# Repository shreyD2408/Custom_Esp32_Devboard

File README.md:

# SD2408 Devboard V1

When designing compact mobile robots, such as miniature rovers, self-balancing walkers, or desktop mecanum platforms—builders almost universally hit a frustrating physical bottleneck: the "breadboard jungle." Connecting an ESP32 microcontroller to external motor drivers, motion sensors, audio amplifiers, and servo breakout boards usually requires a rats' nest of jumper wires, perfboards, and loose cables. Every vibration from a motor risks shaking a loose DuPont connector loose, leading to intermittent power faults, debugging nightmares, and fragile hardware.

This project was built to solve that exact pain point from the ground up: an all-in-one, purpose-built development board that integrates every essential subsystem needed for intelligent, agile robotics onto a single, robust printed circuit board.

# How it Works

1. ESP32-S3-MINI-1: Processes information, reads data, and sends data to different parts of the board through firmware.
2. Motor Drivers: Control power and polarity of the brushed DC motors using either the USB-C power or external 5V input.
3. Four motor terminal connectors: Provide connection points for the DC motors for intended motor configuration.
4. Power Output Points: Designated 5V and GND power outputs for external components.
5. MPU6050: Measures tilt in radians (or if converted, degrees), and acceleration.
6. Audio output: Allows a compatible speaker to produce sound through the board's audio circuitry.

The components are connected through a custom-designed schematic and PCB layout. The schematic defines the electrical connections, while the PCB layout determines where components sit and how electrical signals travel through copper traces.

# Schematic

The schematic shows the electrical connection between all built-in components. Editable schematic available in the **hardware** folder.

# PCB Layout

# 3D Model

The 3D Model shows the physical placement of components, copper traces, and connectors. Editable 3D Model available in the **hardware** folder.

# How to use

Connect the board to a computer through USB-C to program the ESP32-S3 using the Arduino IDE or ESP-IDF. Upload firmware onto the board provided in "firmware" folder for basic features. Firmware can then be used to control motors and servos, read motion data from the MPU6050, and play audio through the MAX98357A amplifier.

External components can be connected through the dedicated motor terminals, servo headers, power outputs, and GPIO, ADC, and I2C headers. Alternatively, a suitable external 5V supply can be connected through the power terminal block. Verify the board's power requirements before connecting motors or servos.

## Bill of Materials (BOM)

| Part | Purpose | Qty | Unit Cost | Total | Vendor |
|---|---|---:|---:|---:|---|
| Panasonic Push Button | User input, BOOT/RESET | 5 | $0.38 | $1.90 | LCSC |
| Ceramic 1µF Capacitor | Decoupling | 50 | $0.01 | $0.50 | LCSC |
| Ceramic 2.2µF Capacitor | Decoupling | 20 | $0.02 | $0.40 | LCSC |
| Ceramic 10µF Capacitor | Filtering | 20 | $0.03 | $0.60 | LCSC |
| Ceramic 100nF Capacitor | Decoupling | 50 | $0.01 | $0.50 | LCSC |
| Ceramic 10nF Capacitor | Filtering | 50 | $0.01 | $0.50 | LCSC |
| Ceramic 220nF Capacitor | Filtering | 2 | $0.33 | $0.66 | LCSC |
| USB-C Connector | Power and programming | 20 | $0.08 | $1.60 | LCSC |
| ESD Protection Diode | Surge protection | 20 | $0.03 | $0.60 | LCSC |
| Fuse | Overcurrent protection | 5 | $0.09 | $0.45 | LCSC |
| MAX98357A | Audio amplifier | 1 | $1.33 | $1.33 | LCSC |
| DRV8833PW | Motor driver | 2 | $1.65 | $3.30 | LCSC |
| LM1117 | 5V to 3.3V regulator | 5 | $0.18 | $0.90 | LCSC |
| USBLC6-2SC6 | USB ESD protection | 10 | $0.05 | $0.50 | LCSC |
| 10K Resistor | Passive component | 100 | $0.01 | $1.00 | LCSC |
| 2.2K Resistor | Passive component | 100 | $0.01 | $1.00 | LCSC |
| 5.1K Resistor | Passive component | 100 | $0.01 | $1.00 | LCSC |
| 1M Resistor | Passive component | 100 | $0.01 | $1.00 | LCSC |
| 1K Resistor | Passive component | 100 | $0.01 | $1.00 | LCSC |
| ESP32-S3-MINI-1 | Main MCU and Wi-Fi | 1 | $4.76 | $4.76 | LCSC |
| 1×2 Terminal Block | Power and motor input | 5 | $0.10 | $0.50 | LCSC |
| 1×3 Terminal Block | Power output | 5 | $0.35 | $1.75 | LCSC |
| LED | Power indicator | 100 | $0.01 | $1.00 | LCSC |
| Custom PCB | Component mounting | 5 | $2.60 | $13.00 | JLCPCB |

**Links available in BOM.md**

### Cost Summary

| Item | Cost |
|---|---:|
| Parts Subtotal | $39.75 |
| Tax & Shipping | $17.36 |
| **Grand Total** | **$57.11 USD** |

**Disclaimer** - Quantities are not exact as LCSC sells in bulk.

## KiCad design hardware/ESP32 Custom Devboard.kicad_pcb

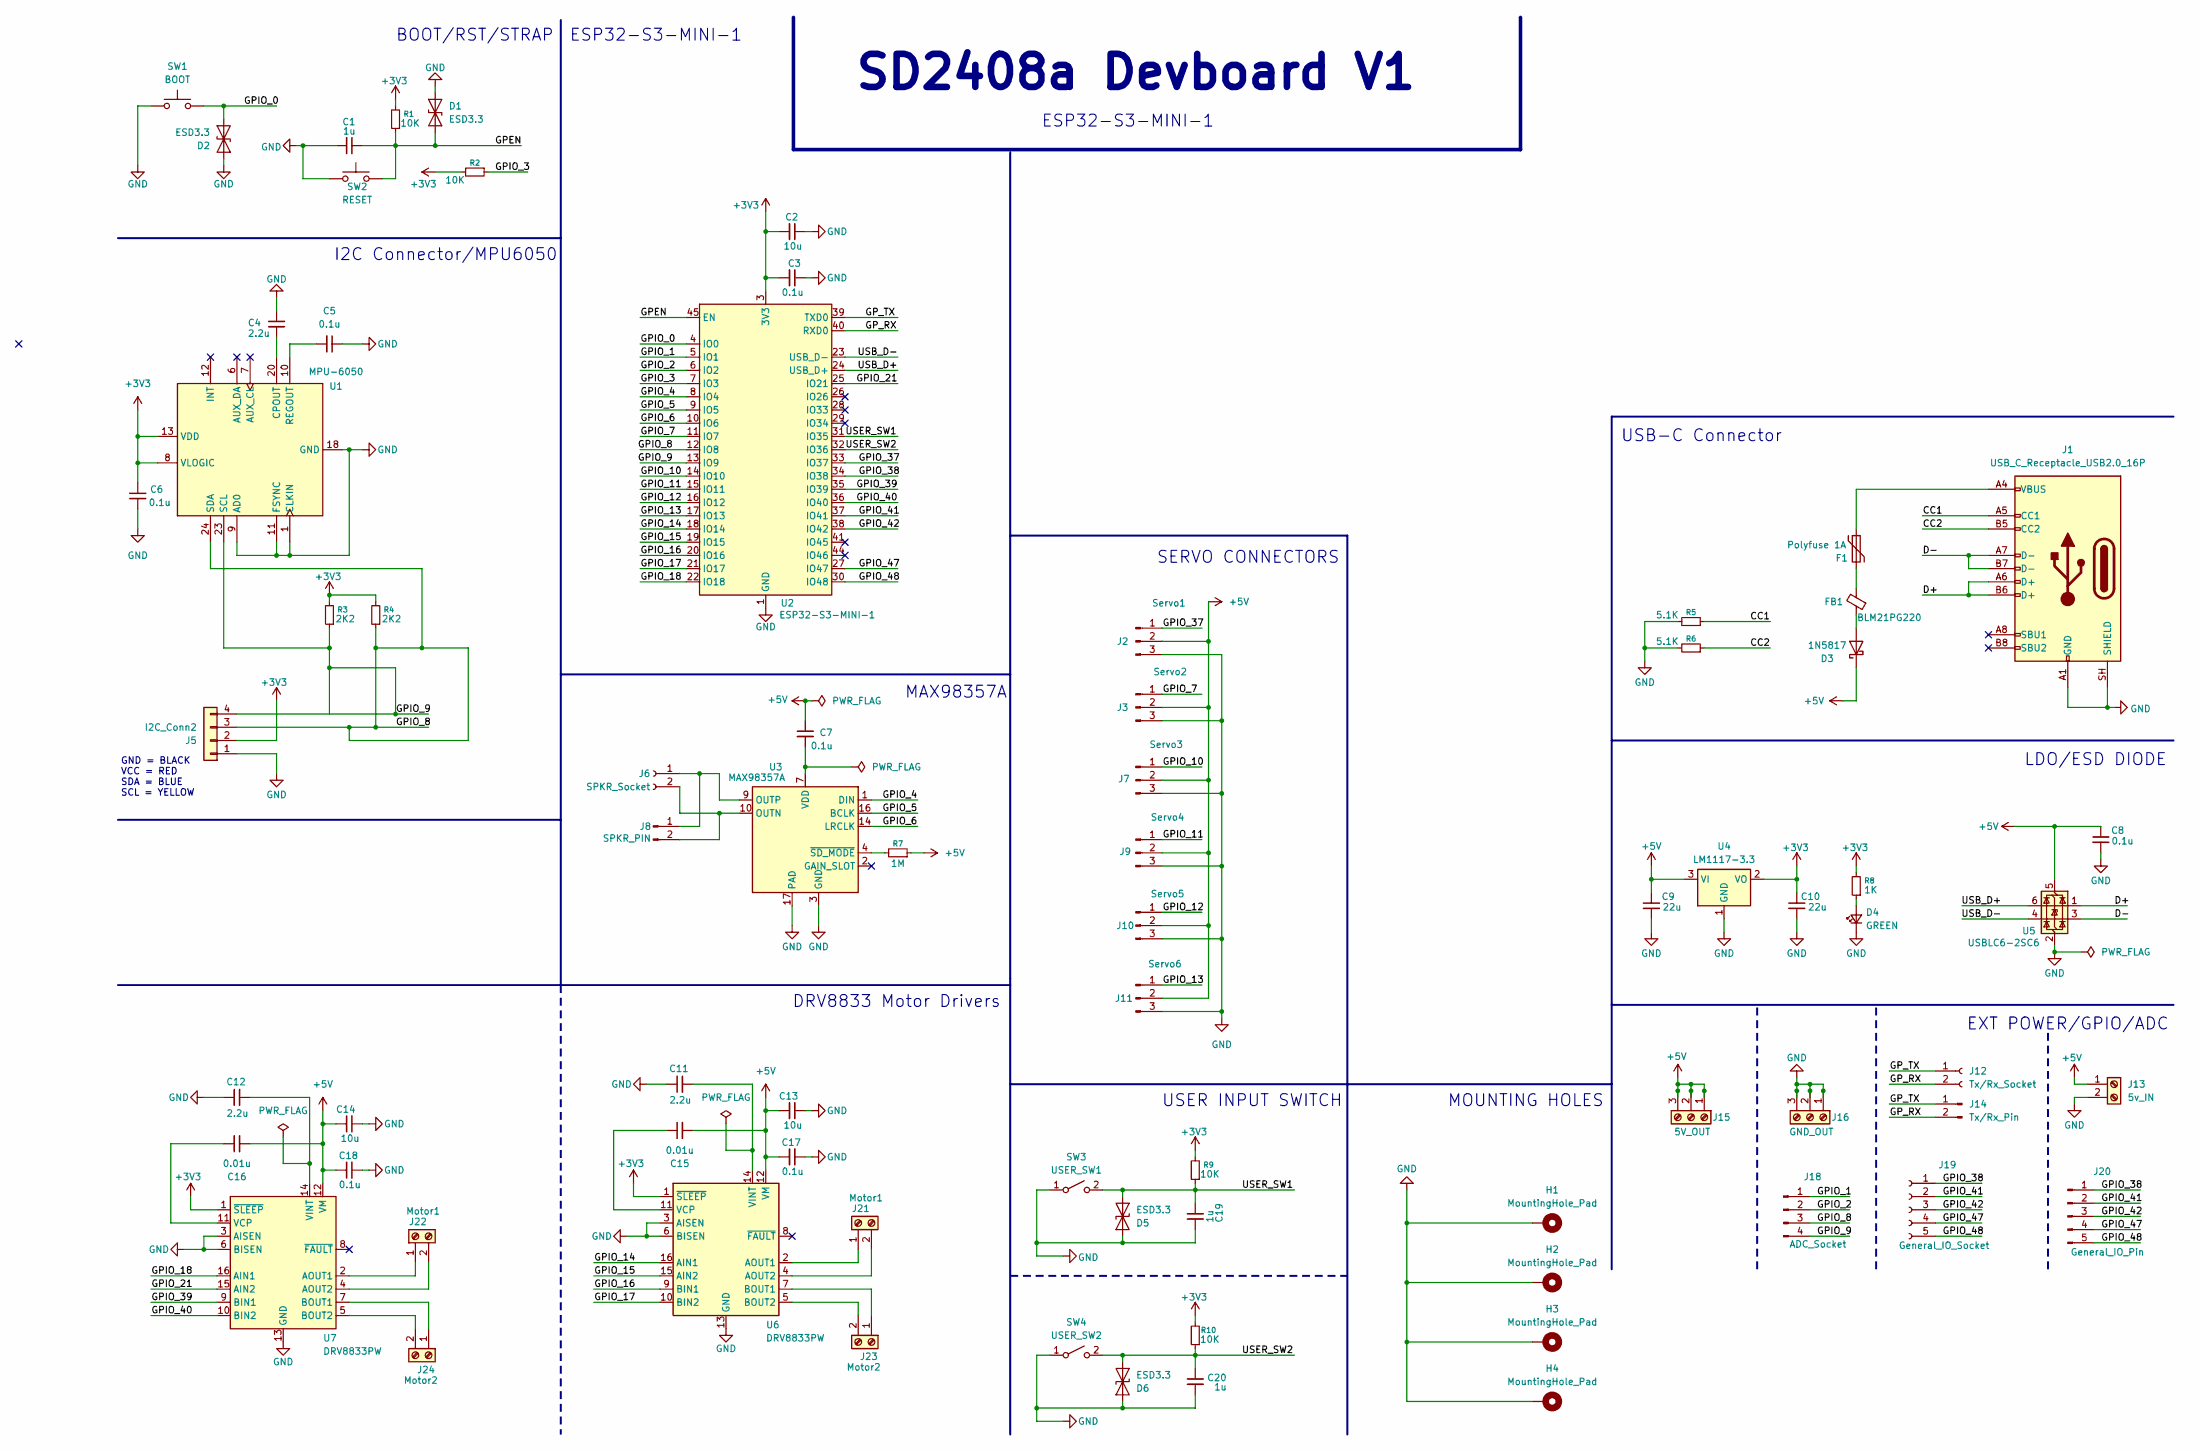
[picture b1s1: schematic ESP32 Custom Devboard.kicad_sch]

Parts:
C1, C19, C20: 1u; C_0201_0603Metric_Pad0.64x0.40mm_HandSolder
C2, C13, C14: 10u; C_0402_1005Metric_Pad0.74x0.62mm_HandSolder
C3, C5, C6, C7, C8, C17, C18: 0.1u; C_0402_1005Metric_Pad0.74x0.62mm_HandSolder
C4, C11, C12: 2.2u; C_0201_0603Metric_Pad0.64x0.40mm_HandSolder
C9, C10: 22u; C_1825_4564Metric_Pad1.57x6.80mm_HandSolder
C15, C16: 0.01u; C_1206_3216Metric_Pad1.33x1.80mm_HandSolder
D1, D2, D5, D6: ESD3.3; D_SOD-923
D3: 1N5817; D_DO-41_SOD81_P10.16mm_Horizontal
D4: GREEN; LED_0402_1005Metric_Pad0.77x0.64mm_HandSolder
F1: Polyfuse 1A; Fuse_1206_3216Metric
FB1: BLM21PG220; L_0805_2012Metric_Pad1.05x1.20mm_HandSolder
H1, H2, H3, H4: MountingHole_Pad; MountingHole_3.2mm_M3_DIN965_Pad
J1: USB_C_Receptacle_USB2.0_16P; USB_C_Receptacle_HCTL_HC-TYPE-C-16P-01A
J2: Servo1; PinHeader_1x03_P2.54mm_Vertical
J3: Servo2; PinHeader_1x03_P2.54mm_Vertical
J5: I2C_Conn2; PinSocket_1x04_P2.54mm_Vertical
J6: SPKR_Socket; PinSocket_1x02_P2.54mm_Vertical
J7: Servo3; PinHeader_1x03_P2.54mm_Vertical
J8: SPKR_PIN; PinHeader_1x02_P2.54mm_Vertical
J9: Servo4; PinHeader_1x03_P2.54mm_Vertical
J10: Servo5; PinHeader_1x03_P2.54mm_Vertical
J11: Servo6; PinHeader_1x03_P2.54mm_Vertical
J12: Tx/Rx_Socket; PinSocket_1x02_P2.54mm_Vertical
J13: 5v_IN; TerminalBlock_4Ucon_1x02_P3.50mm_Horizontal
J14: Tx/Rx_Pin; PinHeader_1x02_P2.54mm_Vertical
J15: 5V_OUT; TerminalBlock_Xinya_XY308-2.54-3P_1x03_P2.54mm_Horizontal
J16: GND_OUT; TerminalBlock_Xinya_XY308-2.54-3P_1x03_P2.54mm_Horizontal
J18: ADC_Socket; PinSocket_1x04_P2.54mm_Vertical
J19: General_IO_Socket; PinSocket_1x05_P2.54mm_Vertical
J20: General_IO_Pin; PinHeader_1x05_P2.54mm_Vertical
J21, J22: Motor1; TerminalBlock_4Ucon_1x02_P3.50mm_Horizontal
J23, J24: Motor2; TerminalBlock_4Ucon_1x02_P3.50mm_Horizontal
R1, R2, R9, R10: 10K; R_0402_1005Metric_Pad0.72x0.64mm_HandSolder
R3, R4: 2K2; R_0402_1005Metric_Pad0.72x0.64mm_HandSolder
R5, R6: 5.1K; R_0402_1005Metric_Pad0.72x0.64mm_HandSolder
R7: 1M; R_0402_1005Metric_Pad0.72x0.64mm_HandSolder
R8: 1K; R_0402_1005Metric_Pad0.72x0.64mm_HandSolder
SW1: BOOT; DIP-24_W7.62mm
SW2: RESET; DIP-24_W7.62mm
SW3: USER_SW1; SW_SPST_EVQP2_ShortPushTravel_H2.1mm
SW4: USER_SW2; SW_SPST_EVQP2_ShortPushTravel_H2.1mm
U1: MPU-6050; InvenSense_QFN-24_4x4mm_P0.5mm
U2: ESP32-S3-MINI-1; ESP32-S2-MINI-1
U3: MAX98357A; TQFN-16-1EP_3x3mm_P0.5mm_EP1.23x1.23mm
U4: LM1117-3.3; SOT-223-3_TabPin2
U5: USBLC6-2SC6; SOT-23-6
U6, U7: DRV8833PW; TSSOP-16_4.4x5mm_P0.65mm

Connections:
+3V3: C2.2, C3.2, C6.1, C10.1, J5.2, R1.2, R2.2, R3.2, R4.2, R8.2, R9.2, R10.2, U1.8 (VLOGIC), U1.13 (VDD), U2.3 (3V3), U4.2 (VO), U6.1 (~SLEEP), U7.1 (~SLEEP)
+5V: C7.2, C8.1, C9.1, C13.2, C14.2, C15.2, C16.2, C17.2, C18.2, D3.1 (K), J2.2, J3.2, J7.2, J9.2, J10.2, J11.2, J13.1, J15.1, J15.2, J15.3, R7.1, U4.3 (VI), U5.5 (VBUS), U6.12 (VM), U7.12 (VM)
/CC1: J1.A5 (CC1), R5.1
/CC2: J1.B5 (CC2), R6.1
/D+: J1.A6 (D+), J1.B6 (D+), U5.1 (I/O1)
/D-: J1.A7 (D-), J1.B7 (D-), U5.3 (I/O2)
/GPEN: C1.1, D1.1 (A1), R1.1, SW2.2 (B), U2.45 (EN)
/GPIO_0: D2.1 (A1), SW1.2 (B), U2.4 (IO0)
/GPIO_1: J18.1, U2.5 (IO1)
/GPIO_2: J18.2, U2.6 (IO2)
/GPIO_3: R2.1, U2.7 (IO3)
/GPIO_4: U2.8 (IO4), U3.1 (DIN)
/GPIO_5: U2.9 (IO5), U3.16 (BCLK)
/GPIO_6: U2.10 (IO6), U3.14 (LRCLK)
/GPIO_7: J3.1, U2.11 (IO7)
/GPIO_8: J5.3, J18.3, R4.1, U1.24 (SDA), U2.12 (IO8)
/GPIO_9: J5.4, J18.4, R3.1, U1.23 (SCL), U2.13 (IO9)
/GPIO_10: J7.1, U2.14 (IO10)
/GPIO_11: J9.1, U2.15 (IO11)
/GPIO_12: J10.1, U2.16 (IO12)
/GPIO_13: J11.1, U2.17 (IO13)
/GPIO_14: U2.18 (IO14), U6.16 (AIN1)
/GPIO_15: U2.19 (IO15), U6.15 (AIN2)
/GPIO_16: U2.20 (IO16), U6.9 (BIN1)
/GPIO_17: U2.21 (IO17), U6.10 (BIN2)
/GPIO_18: U2.22 (IO18), U7.16 (AIN1)
/GPIO_21: U2.25 (IO21), U7.15 (AIN2)
/GPIO_37: J2.1, U2.33 (IO37)
/GPIO_38: J19.1, J20.1, U2.34 (IO38)
/GPIO_39: U2.35 (IO39), U7.9 (BIN1)
/GPIO_40: U2.36 (IO40), U7.10 (BIN2)
/GPIO_41: J19.2, J20.2, U2.37 (IO41)
/GPIO_42: J19.3, J20.3, U2.38 (IO42)
/GPIO_47: J19.4, J20.4, U2.27 (IO47)
/GPIO_48: J19.5, J20.5, U2.30 (IO48)
/GP_RX: J12.2, J14.2, U2.40 (RXD0)
/GP_TX: J12.1, J14.1, U2.39 (TXD0)
/USB_D+: U2.24 (USB_D+), U5.6 (I/O1)
/USB_D-: U2.23 (USB_D-), U5.4 (I/O2)
/USER_SW1: C19.2, D5.1 (A1), R9.1, SW3.2 (B), U2.31 (IO35)
/USER_SW2: C20.2, D6.1 (A1), R10.1, SW4.2 (B), U2.32 (IO36)
GND: C1.2, C2.1, C3.1, C4.1, C5.2, C6.2, C8.2, C9.2, C10.2, C11.2, C12.2, C13.1, C14.1, C17.1, C18.1, C19.1, C20.1, D1.2 (A2), D2.2 (A2), D4.1 (K), D5.2 (A2), D6.2 (A2), H1.1 (1_1), H2.1 (1_1), H3.1 (1_1), H4.1 (1_1), J1.A1 (GND), J1.A12 (GND), J1.B1 (GND), J1.B12 (GND), J1.SH (SHIELD), J2.3, J3.3, J5.1, J7.3, J9.3, J10.3, J11.3, J13.2, J16.1, J16.2, J16.3, R5.2, R6.2, SW1.1 (A), SW2.1 (A), SW3.1 (A), SW4.1 (A), U1.1 (CLKIN), U1.9 (AD0), U1.11 (FSYNC), U1.18 (GND), U2.1 (GND), U2.2 (GND), U2.42 (GND), U2.43 (GND), U2.46 (GND), U2.47 (GND), U2.48 (GND), U2.49 (GND), U2.50 (GND), U2.51 (GND), U2.52 (GND), U2.53 (GND), U2.54 (GND), U2.55 (GND), U2.56 (GND), U2.57 (GND), U2.58 (GND), U2.59 (GND), U2.60 (GND), U2.61 (GND), U2.62 (GND), U2.63 (GND), U2.64 (GND), U2.65 (GND), U3.3 (GND), U3.11 (GND), U3.15 (GND), U3.17 (PAD), U4.1 (GND), U5.2 (GND), U6.3 (AISEN), U6.6 (BISEN), U6.13 (GND), U7.3 (AISEN), U7.6 (BISEN), U7.13 (GND)
unnamed: C7.1, U3.7 (VDD), U3.8 (VDD)
unnamed: D3.2 (A), FB1.1
unnamed: D4.2 (A), R8.1
unnamed: F1.1, J1.A4 (VBUS), J1.A9 (VBUS), J1.B4 (VBUS), J1.B9 (VBUS)
unnamed: F1.2, FB1.2
unnamed: J6.1, J8.1, U3.9 (OUTP)
unnamed: J6.2, J8.2, U3.10 (OUTN)
unnamed: J21.1, U6.2 (AOUT1)
unnamed: J21.2, U6.4 (AOUT2)
unnamed: J22.1, U7.2 (AOUT1)
unnamed: J22.2, U7.4 (AOUT2)
unnamed: J23.1, U6.7 (BOUT1)
unnamed: J23.2, U6.5 (BOUT2)
unnamed: J24.1, U7.7 (BOUT1)
unnamed: J24.2, U7.5 (BOUT2)
unnamed: C4.2, U1.20 (CPOUT)
unnamed: C5.1, U1.10 (REGOUT)
unnamed: R7.2, U3.4 (~SD_MODE)
unnamed: C15.1, U6.11 (VCP)
unnamed: C11.1, U6.14 (VINT)
unnamed: C16.1, U7.11 (VCP)
unnamed: C12.1, U7.14 (VINT)

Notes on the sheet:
DRV8833 Motor Drivers
MOUNTING HOLES
ESP32-S3-MINI-1
I2C Connector/MPU6050
SD2408a Devboard V1
ESP32-S3-MINI-1
MAX98357A
LDO/ESD DIODE
GND = BLACK VCC = RED SDA = BLUE SCL = YELLOW
EXT POWER/GPIO/ADC
BOOT/RST/STRAP
USER INPUT SWITCH
USB-C Connector
SERVO CONNECTORS

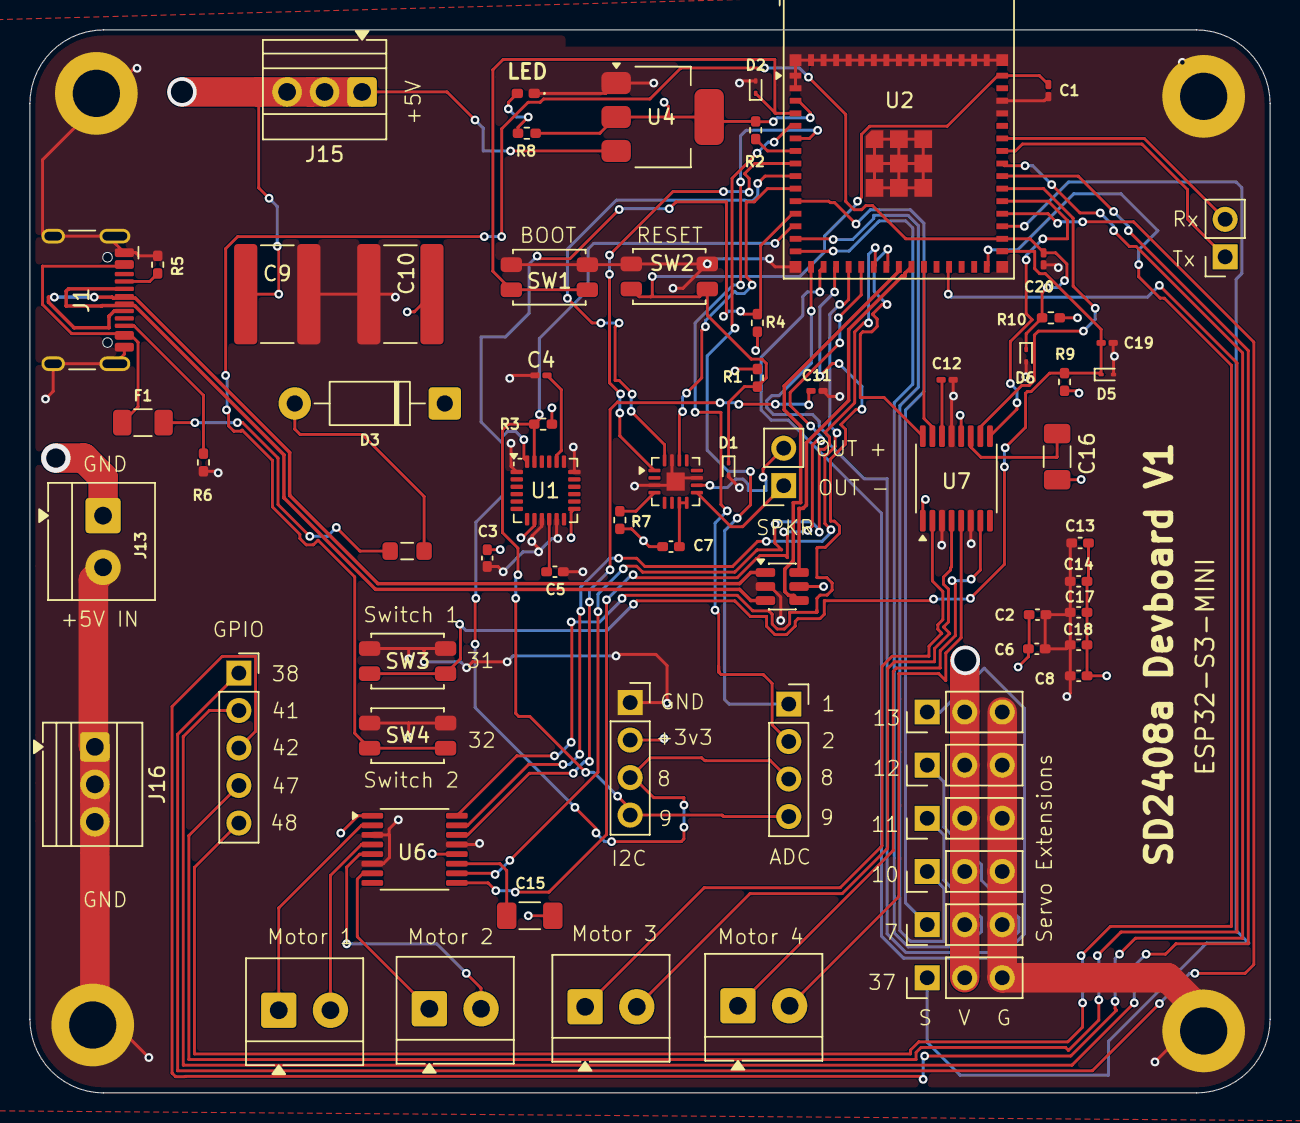
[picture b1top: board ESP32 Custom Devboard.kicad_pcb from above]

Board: 4 copper layers, 84.0 x 72.0 mm, 72 parts (0 on the bottom side), 64 nets.

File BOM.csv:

"Reference","Qty","Value","DNP","Exclude from BOM","Exclude from Board","Exclude from Simulation","Exclude from Position Files","Footprint","Datasheet"
"SW3","1","USER_SW1","","","","","${EXCLUDE_FROM_POS_FILES}","Button_Switch_SMD:SW_SPST_EVQP2_ShortPushTravel_H2.1mm",""
"SW4","1","USER_SW2","","","","","${EXCLUDE_FROM_POS_FILES}","Button_Switch_SMD:SW_SPST_EVQP2_ShortPushTravel_H2.1mm",""
"C1,C19,C20","3","1u","","","","","${EXCLUDE_FROM_POS_FILES}","Capacitor_SMD:C_0201_0603Metric_Pad0.64x0.40mm_HandSolder",""
"C4,C11,C12","3","2.2u","","","","","${EXCLUDE_FROM_POS_FILES}","Capacitor_SMD:C_0201_0603Metric_Pad0.64x0.40mm_HandSolder",""
"C2,C13,C14","3","10u","","","","","${EXCLUDE_FROM_POS_FILES}","Capacitor_SMD:C_0402_1005Metric_Pad0.74x0.62mm_HandSolder",""
"C3,C5,C6,C7,C8,C17,C18","7","0.1u","","","","","${EXCLUDE_FROM_POS_FILES}","Capacitor_SMD:C_0402_1005Metric_Pad0.74x0.62mm_HandSolder",""
"C15,C16","2","0.01u","","","","","${EXCLUDE_FROM_POS_FILES}","Capacitor_SMD:C_1206_3216Metric_Pad1.33x1.80mm_HandSolder",""
"C9,C10","2","22u","","","","","${EXCLUDE_FROM_POS_FILES}","Capacitor_SMD:C_1825_4564Metric_Pad1.57x6.80mm_HandSolder",""
"J1","1","USB_C_Receptacle_USB2.0_16P","","","","","${EXCLUDE_FROM_POS_FILES}","Connector_USB:USB_C_Receptacle_HCTL_HC-TYPE-C-16P-01A","https://www.usb.org/sites/default/files/documents/usb_type-c.zip"
"D1,D2,D5,D6","4","ESD3.3","","","","","${EXCLUDE_FROM_POS_FILES}","Diode_SMD:D_SOD-923","https://www.onsemi.com/pub/Collateral/ESD9B-D.PDF"
"F1","1","Polyfuse 1A","","","","","${EXCLUDE_FROM_POS_FILES}","Fuse:Fuse_1206_3216Metric",""
"FB1","1","BLM21PG220","","","","","${EXCLUDE_FROM_POS_FILES}","Inductor_SMD:L_0805_2012Metric_Pad1.05x1.20mm_HandSolder",""
"D4","1","GREEN","","","","","${EXCLUDE_FROM_POS_FILES}","LED_SMD:LED_0402_1005Metric_Pad0.77x0.64mm_HandSolder",""
"U3","1","MAX98357A","","","","","${EXCLUDE_FROM_POS_FILES}","Package_DFN_QFN:TQFN-16-1EP_3x3mm_P0.5mm_EP1.23x1.23mm","https://www.analog.com/media/en/technical-documentation/data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"
"SW1","1","BOOT","","","","","${EXCLUDE_FROM_POS_FILES}","Package_DIP:DIP-24_W7.62mm",""
"SW2","1","RESET","","","","","${EXCLUDE_FROM_POS_FILES}","Package_DIP:DIP-24_W7.62mm",""
"U6,U7","2","DRV8833PW","","","","","${EXCLUDE_FROM_POS_FILES}","Package_SO:TSSOP-16_4.4x5mm_P0.65mm","http://www.ti.com/lit/ds/symlink/drv8833.pdf"
"U4","1","LM1117-3.3","","","","","${EXCLUDE_FROM_POS_FILES}","Package_TO_SOT_SMD:SOT-223-3_TabPin2","http://www.ti.com/lit/ds/symlink/lm1117.pdf"
"U5","1","USBLC6-2SC6","","","","","${EXCLUDE_FROM_POS_FILES}","Package_TO_SOT_SMD:SOT-23-6","https://www.st.com/resource/en/datasheet/usblc6-2.pdf"
"R1,R2,R9,R10","4","10K","","","","","${EXCLUDE_FROM_POS_FILES}","Resistor_SMD:R_0402_1005Metric_Pad0.72x0.64mm_HandSolder",""
"R3,R4","2","2K2","","","","","${EXCLUDE_FROM_POS_FILES}","Resistor_SMD:R_0402_1005Metric_Pad0.72x0.64mm_HandSolder",""
"R5,R6","2","5.1K","","","","","${EXCLUDE_FROM_POS_FILES}","Resistor_SMD:R_0402_1005Metric_Pad0.72x0.64mm_HandSolder",""
"R7","1","1M","","","","","${EXCLUDE_FROM_POS_FILES}","Resistor_SMD:R_0402_1005Metric_Pad0.72x0.64mm_HandSolder",""
"R8","1","1K","","","","","${EXCLUDE_FROM_POS_FILES}","Resistor_SMD:R_0402_1005Metric_Pad0.72x0.64mm_HandSolder",""
"U2","1","ESP32-S3-MINI-1","","","","","${EXCLUDE_FROM_POS_FILES}","RF_Module:ESP32-S2-MINI-1","https://www.espressif.com/sites/default/files/documentation/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"
"J15","1","5V_OUT","","","","","${EXCLUDE_FROM_POS_FILES}","TerminalBlock:TerminalBlock_Xinya_XY308-2.54-3P_1x03_P2.54mm_Horizontal",""
"J16","1","GND_OUT","","","","","${EXCLUDE_FROM_POS_FILES}","TerminalBlock:TerminalBlock_Xinya_XY308-2.54-3P_1x03_P2.54mm_Horizontal",""
"J13","1","5v_IN","","","","","${EXCLUDE_FROM_POS_FILES}","TerminalBlock_4Ucon:TerminalBlock_4Ucon_1x02_P3.50mm_Horizontal",""
"J21,J22","2","Motor1","","","","","${EXCLUDE_FROM_POS_FILES}","TerminalBlock_4Ucon:TerminalBlock_4Ucon_1x02_P3.50mm_Horizontal",""
"J23,J24","2","Motor2","","","","","${EXCLUDE_FROM_POS_FILES}","TerminalBlock_4Ucon:TerminalBlock_4Ucon_1x02_P3.50mm_Horizontal",""
